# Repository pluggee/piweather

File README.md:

# piweather
raspberry pi based system for weather monitoring and automation

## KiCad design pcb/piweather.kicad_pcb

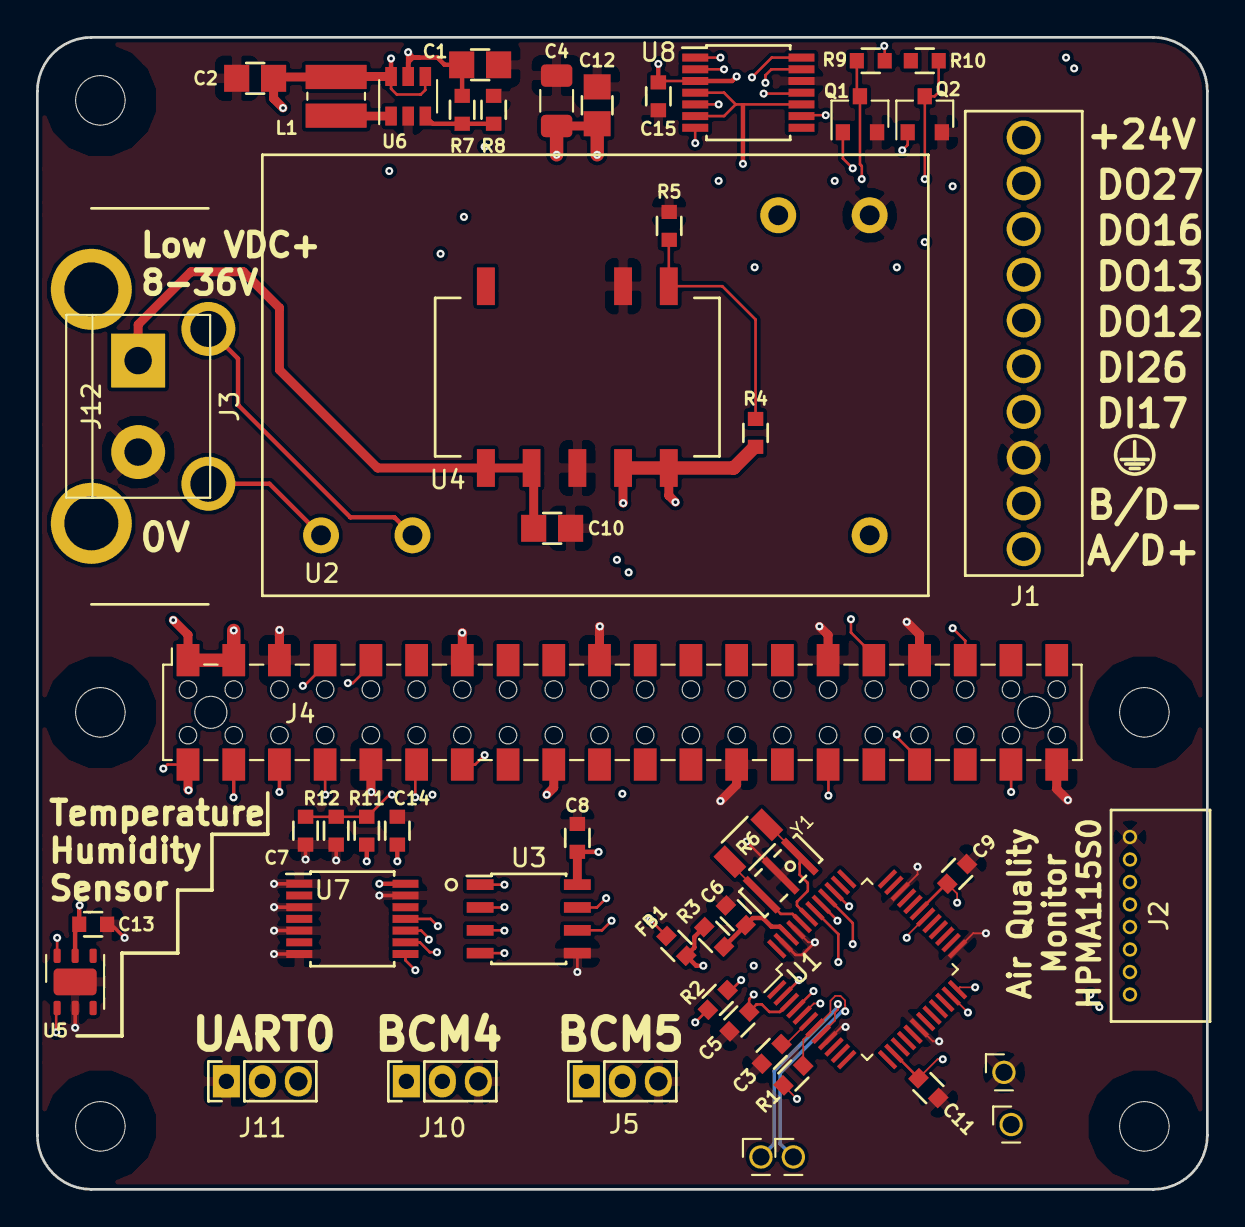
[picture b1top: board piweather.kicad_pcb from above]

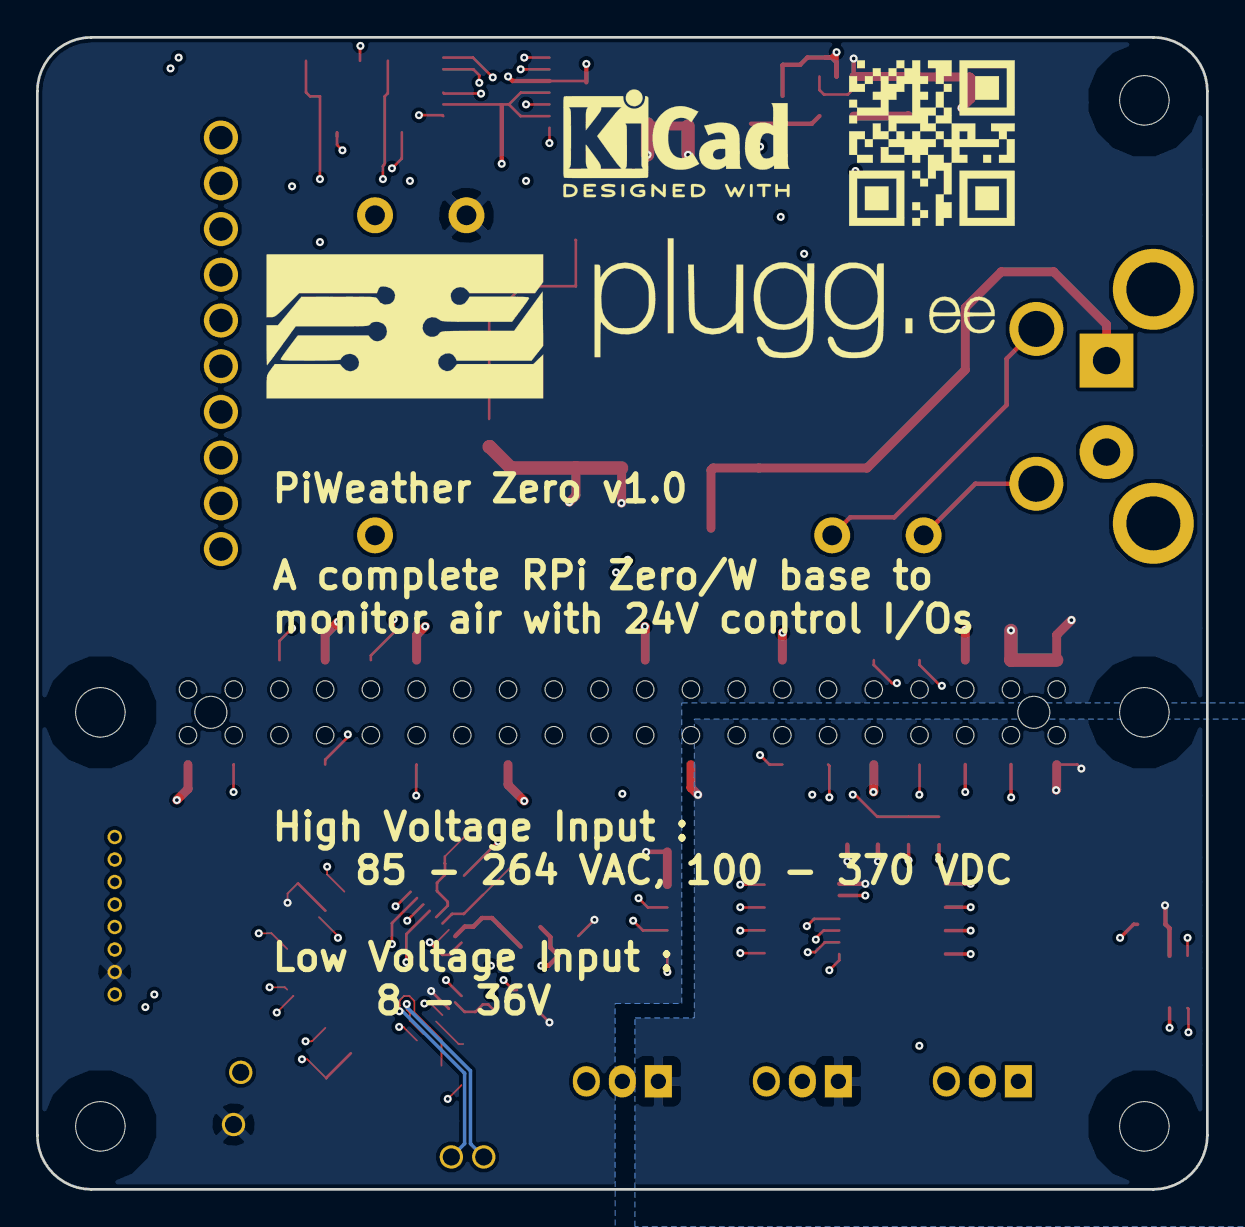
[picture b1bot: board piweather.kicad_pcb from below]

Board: 4 copper layers, 65.0 x 64.0 mm, 60 parts (3 on the bottom side), 49 nets.

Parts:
A1: ART; pluggeeLogo
A2: ART; pluggee-QRNEG-127X127
A3: ART; KiCad-Logo2_6mm_SilkScreen
C1, C2, C10, C12: GRM21BR60J476ME15K; CAPC0805
C3: CC0603KRX7R9BB333; CAPC0603
C4: CP; C_1206_3216Metric
C5, C6, C7, C8, C9, C11, C13, C14, C15: CC0603KRX7R9BB104; CAPC0603
FB1: Ferrite_Bead_Small; CAPC0603
H1, H2, H3, H4, H6: MountingHole; RPi_Hat_Mounting_Hole
J1: Screw_Terminal_01x10; Terminal_block_OSTVN10A150
J2: Conn_01x08_Male; PICOBLADE_FEMALE_8
J3: Screw_Terminal_01x02; TerminalBlock_1X2_P5.08mm
J4: Raspberry_Pi_2_3; RPi_2x20_SMT
J5, J10, J11: Conn_01x03_Male; SOCKET200P-01X03-S3B-PH-K-S(LF)(SN)
J6, J7, J8, J9: Conn_01x01_Male; POGOPIN_5mm_P70-2300045R
J12: Conn_01x02_Male; AC_terminal_4300.0104
L1: L; L_Wuerth_MAPI-3020
Q1, Q2: 2N7002; SOT-23
R1: RC0603FR-071K5L; RESC0603
R2, R4, R5: RC0603FR-0710KL; RESC0603
R3: RC0603FR-07475RL; RESC0603
R6: RC1206FR-071ML; RESC1206
R7: RC0603FR-071ML; RESC0603
R8: RC0603FR-0734KL; RESC0603
R9, R10, R11, R12: RC0603FR-0730K1L; RESC0603
U1: FT2232D; LQFP-48_7x7mm_P0.5mm
U2: PSK-S5B-5
U3: THVD1500; SOIC127P490X390X175-8
U4: V78E05-1000-SMT-TR
U5: Si7020-A20; DFN-6-1EP_3x3mm_P1mm_EP1.5x2.4mm
U6: TLV61046ADB; SOT-23-6
U7: 74HC14; TSSOP-14_4.4x5mm_P0.65mm
U8: LM339; TSSOP-14_4.4x5mm_P0.65mm
Y1: Resonator; RESONTATOR_450X200

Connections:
+3V3: C13.2, C14.1, J4.1, J4.17, J5.1, J10.1, R9.1, R10.1, R11.1, U5.5, U7.14
+5V: C2.1, C4.1, C8.1, C9.2, C12.1, FB1.1, J2.2, J4.2, J4.4, J6.1, L1.1, R2.2, R4.1, U1.4, U1.31, U2.16, U3.8, U4.4, U4.5, U6.4, U6.6
+24V: C1.1, C15.1, J1.10, R7.1, U6.5, U8.3
/3V3OUT: C3.1, U1.6
/AC_L: J12.1, U2.1
/AC_N: J12.2, U2.3
/AVCC: C6.1, R3.2, U1.46
/BCM4_PIN7: J4.7, J10.2
/BCM5_PIN29: J4.29, J5.2
/BCM17_PIN11: J4.11, U7.8
/BCM26_PIN37: J4.37, U7.10
/DI17: J1.4, Q1.1
/DI26: J1.5, Q2.1
/DO12: J1.6, U8.2
/DO13: J1.7, U8.13
/DO16: J1.8, U8.14
/DO27: J1.9, U8.1
/EEDATA: R2.1, U1.2
/FB_BOOST: R7.2, R8.1, U6.3
/FB_DCDC: R4.2, R5.1, U4.6
/IN_24V: C10.1, J3.1, U4.1, U4.2
/P0_RXD: J4.10, J11.3
/P0_TXD: J4.8, J11.2
/P1_3V3: C11.1, J2.1, U1.14
/P1_RXD_HW_TXD: J2.6, U1.23
/P1_TXD_HW_RXD: J2.7, U1.24
/P2_D: U1.40, U3.4
/P2_R: U1.39, U3.1
/P2_~RE: U1.41, U3.2
/P_DE: U1.30, U3.3
/SCL: J4.5, U5.6
/SDA: J4.3, U5.1
/SW_BOOST: L1.2, U6.1
/USBD_N: J9.1, U1.8
/USBD_P: J8.1, R1.1, U1.7
/VCC_FTDI: C5.1, FB1.2, R3.1, U1.3, U1.42
/XTIN: R6.1, U1.43, Y1.1
/XTOUT: R6.2, U1.44, Y1.3
/~RSTOUT: R1.2, U1.5
BCM12: J4.32, U8.5
BCM13: J4.33, U8.11
BCM16: J4.36, U8.9
BCM27: J4.13, U8.7
GND: C1.2, C2.2, C3.2, C4.2, C5.2, C6.2, C7.2, C8.2, C9.1, C10.2, C11.2, C12.2, C13.1, C14.2, C15.2, J1.3, J2.8, J3.2, J4.6, J4.9, J4.14, J4.20, J4.25, J4.30, J4.34, J4.39, J5.3, J7.1, J10.3, J11.1, Q1.2, Q2.2, R5.2, R8.2, R12.2, U1.9, U1.18, U1.25, U1.34, U1.45, U1.47, U2.14, U3.5, U4.3, U4.7, U5.2, U5.7, U6.2, U7.1, U7.3, U7.5, U7.7, U7.13, U8.12, Y1.2
REF3V3: C7.1, R11.2, R12.1, U8.4, U8.6, U8.8, U8.10
RS485_A: J1.1, U3.6
RS485_B: J1.2, U3.7
~BCM17: Q1.3, R9.2, U7.9
~BCM26: Q2.3, R10.2, U7.11

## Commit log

2019-10-03 first commit, clone from an existing project
2019-10-11 wip, needs routing
2019-10-15 started passive placement
2019-10-15 wip, more placement
2019-10-21 updated placement, will start routing
2019-10-29 layout in progress
2019-10-30 routing in progress
2019-10-31 preparing for first release
2019-11-01 added BOM
2019-11-01 regenerated gerbers
2022-07-15 migrated to kicad 6
